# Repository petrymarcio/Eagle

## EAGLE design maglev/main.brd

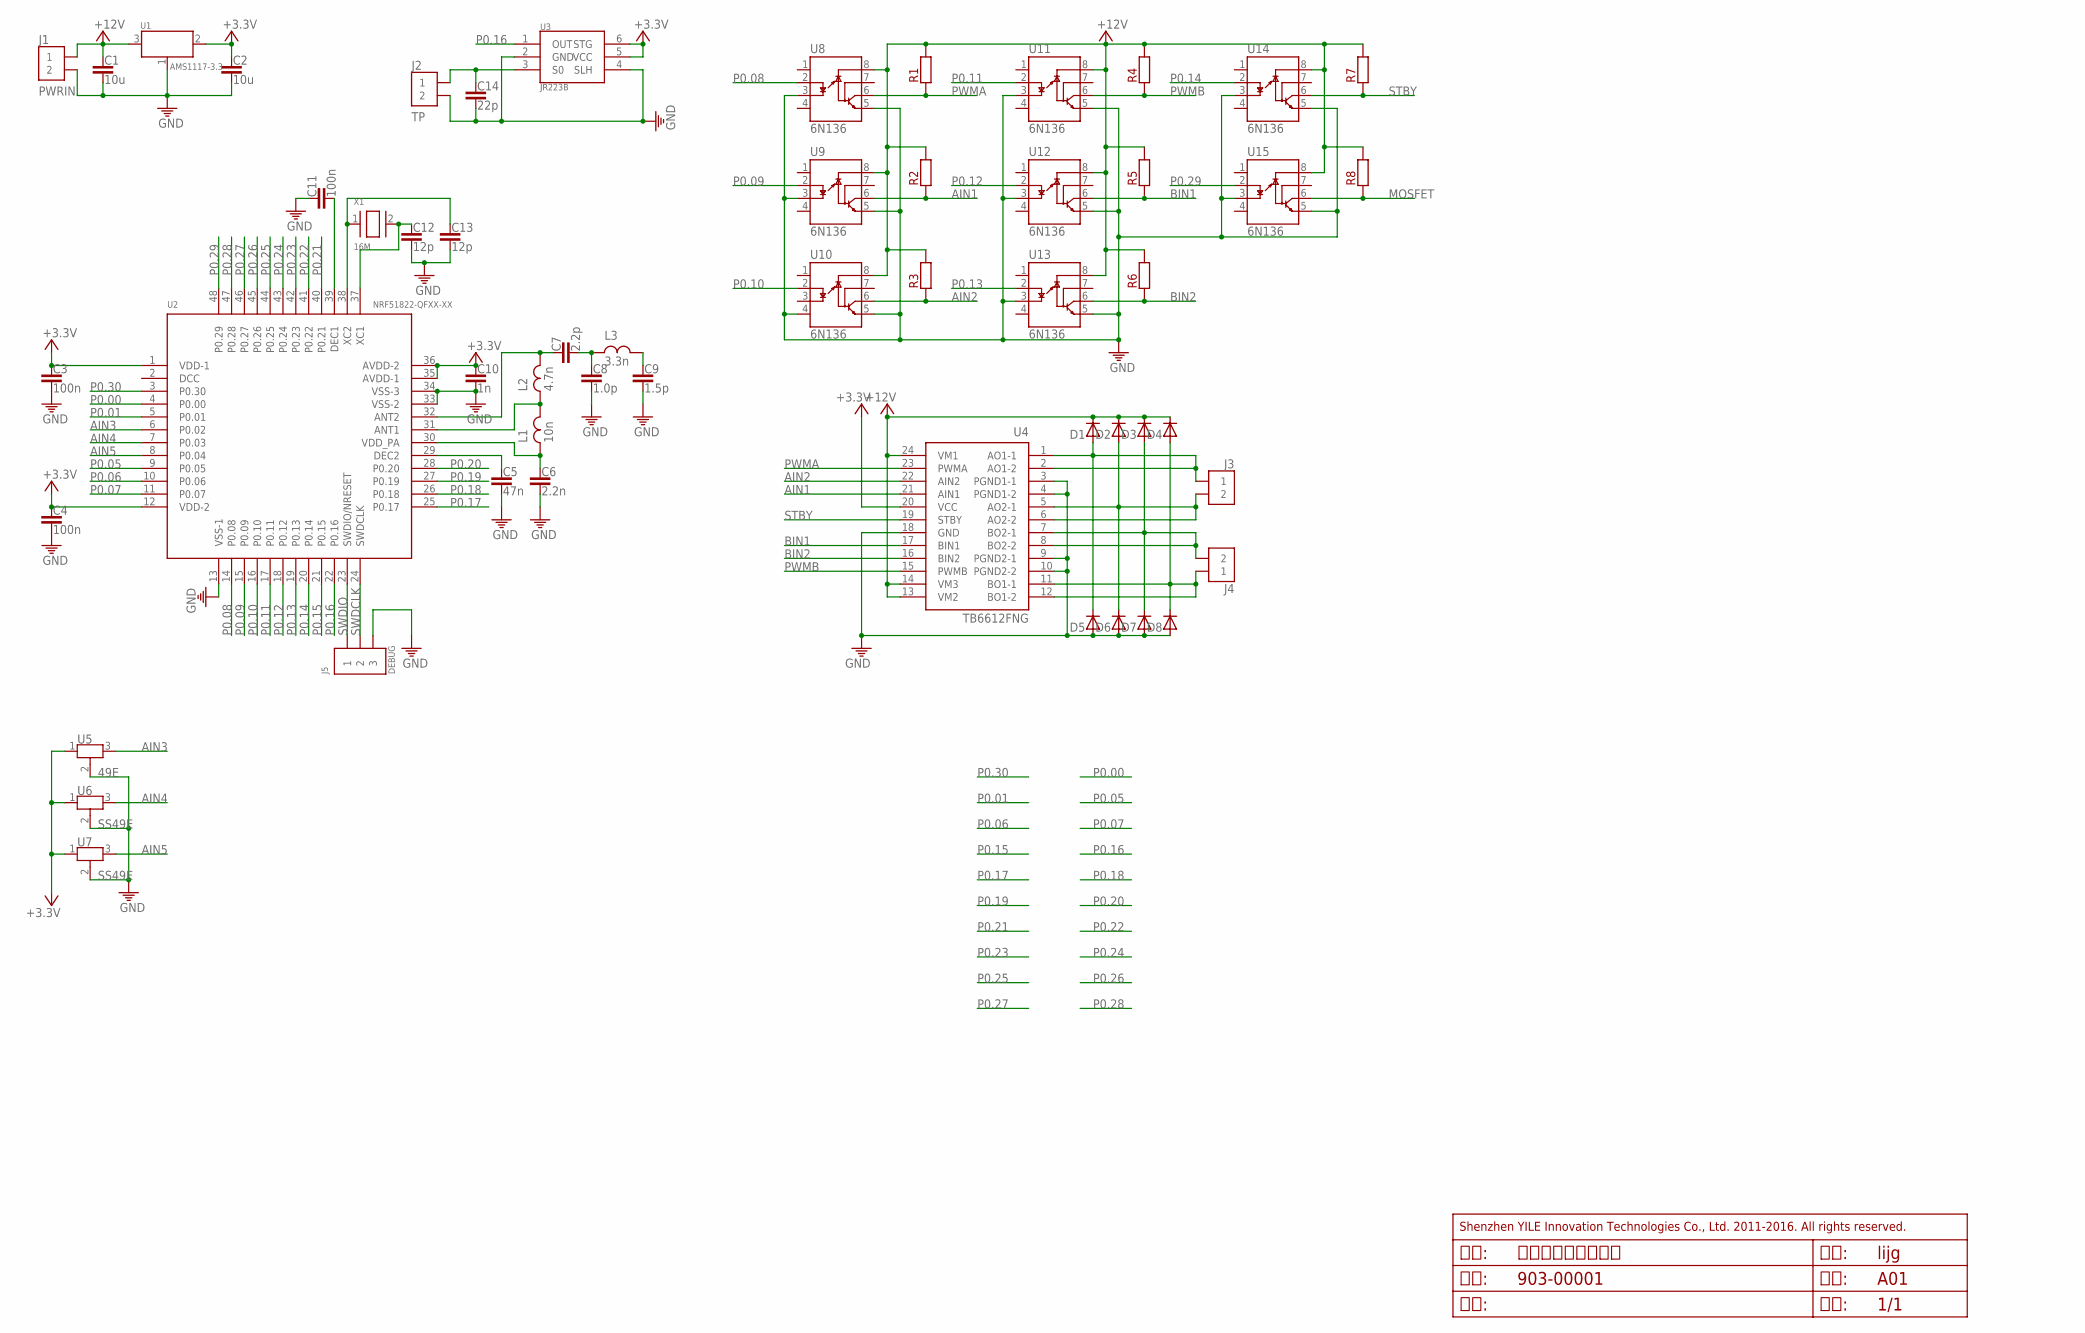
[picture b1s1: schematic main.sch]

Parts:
C1, C2: 10u; 0805
C3, C4, C11: 100n; 0805
C5: 47n; 0805
C6: 2.2n; 0805
C7: 2.2p; 0805
C8: 1.0p; 0805
C9: 1.5p; 0805
C10: 1n; 0805
C12, C13: 12p; 0805
C14: 22p; 0805
D1, D2, D3, D4, D5, D6, D7, D8: D0805; 0805
J1: PWRIN; SIP2-100
J2: TP; SIP2-100
J3, J4: CON2X12X1-DIP2-100; SIP2-100
J5: DEBUG; SIP3-100
L1: 10n; 0805
L2: 4.7n; 0805
L3: 3.3n; 0805
R1, R2, R3, R4, R5, R6, R7, R8: R0805; 0805
U1: AMS1117-3.3; SOT-223
U2: NRF51822-QFXX-XX; QFN48-6.0A-0.4A
U3: JR223B; SSOP6-P-118-0.6A
U4: TB6612FNG; SSOP24-P-300-0.65A
U5: 49E; AH3503
U6, U7: SS49E; AH3503
U8, U9, U10, U11, U12, U13, U14, U15: 6N136; SOP8-900A-2.54A
X1: 16M; S5032B

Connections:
+3.3V: C2.1, C3.1, C4.1, C10.1, U1.2 (VOUT), U2.1 (VDD-1), U2.12 (VDD-2), U2.35 (AVDD-1), U2.36 (AVDD-2), U3.5 (VCC), U3.6 (STG), U4.20 (VCC), U5.1, U6.1, U7.1
+12V: C1.1, D1.2, D2.2, D3.2, D4.2, J1.P$1 (1), R1.2, R2.2, R3.2, R4.2, R5.2, R6.2, R7.2, R8.2, U1.3 (VIN), U4.13 (VM2), U4.14 (VM3), U4.24 (VM1), U8.8 (VCC), U9.8 (VCC), U10.8 (VCC), U11.8 (VCC), U12.8 (VCC), U13.8 (VCC), U14.8 (VCC), U15.8 (VCC)
AIN1: R2.1, U4.21 (AIN1), U9.6 (VO)
AIN2: R3.1, U4.22 (AIN2), U10.6 (VO)
AIN3: U2.6 (P0.02), U5.3
AIN4: U2.7 (P0.03), U6.3
AIN5: U2.8 (P0.04), U7.3
BIN1: R5.1, U4.17 (BIN1), U12.6 (VO)
BIN2: R6.1, U4.16 (BIN2), U13.6 (VO)
GND: C1.2, C2.2, C3.2, C4.2, C5.2, C6.2, C8.2, C9.2, C10.2, C11.1, C12.2, C13.2, C14.2, D5.1, D6.1, D7.1, D8.1, J1.P$2 (2), J2.P$2 (2), J5.P$3 (3), U1.1 (GND/ADJ), U2.13 (VSS-1), U2.33 (VSS-2), U2.34 (VSS-3), U3.2 (GND), U3.4 (SLH), U4.3 (PGND1-1), U4.4 (PGND1-2), U4.9 (PGND2-1), U4.10 (PGND2-2), U4.18 (GND), U5.2, U6.2, U7.2, U8.3 (C), U8.5 (GND), U9.3 (C), U9.5 (GND), U10.4 (NC2), U10.5 (GND), U11.3 (C), U11.5 (GND), U12.3 (C), U12.5 (GND), U13.3 (C), U13.5 (GND), U14.3 (C), U14.5 (GND), U15.3 (C), U15.5 (GND)
MOSFET: R8.1, U15.6 (VO)
unnamed: C6.1, L1.1, U2.30 (VDD_PA)
unnamed: L1.2, L2.1, U2.31 (ANT1)
unnamed: C5.1, U2.29 (DEC2)
unnamed: C7.1, L2.2, U2.32 (ANT2)
unnamed: C7.2, C8.1, L3.1
unnamed: C14.1, J2.P$1 (1), U3.3 (S0)
unnamed: C12.1, U2.37 (XC1), X1.2 (X2)
unnamed: C13.1, U2.38 (XC2), X1.1 (X1)
unnamed: D1.1, D5.2, J3.P$1 (1), U4.1 (AO1-1), U4.2 (AO1-2)
unnamed: C11.2, U2.39 (DEC1)
unnamed: D2.1, D6.2, J3.P$2 (2), U4.5 (AO2-1), U4.6 (AO2-2)
unnamed: D3.1, D7.2, J4.P$2 (2), U4.7 (BO2-1), U4.8 (BO2-2)
unnamed: D4.1, D8.2, J4.P$1 (1), U4.11 (BO1-1), U4.12 (BO1-2)
P0.00: U2.4 (P0.00)
P0.01: U2.5 (P0.01)
P0.05: U2.9 (P0.05)
P0.06: U2.10 (P0.06)
P0.07: U2.11 (P0.07)
P0.08: U2.14 (P0.08), U8.2 (A)
P0.09: U2.15 (P0.09), U9.2 (A)
P0.10: U2.16 (P0.10), U10.2 (A)
P0.11: U2.17 (P0.11), U11.2 (A)
P0.12: U2.18 (P0.12), U12.2 (A)
P0.13: U2.19 (P0.13), U13.2 (A)
P0.14: U2.20 (P0.14), U14.2 (A)
P0.15: U2.21 (P0.15)
P0.16: U2.22 (P0.16), U3.1 (OUT)
P0.17: U2.25 (P0.17)
P0.18: U2.26 (P0.18)
P0.19: U2.27 (P0.19)
P0.20: U2.28 (P0.20)
P0.21: U2.40 (P0.21)
P0.22: U2.41 (P0.22)
P0.23: U2.42 (P0.23)
P0.24: U2.43 (P0.24)
P0.25: U2.44 (P0.25)
P0.26: U2.45 (P0.26)
P0.27: U2.46 (P0.27)
P0.28: U2.47 (P0.28)
P0.29: U2.48 (P0.29), U15.2 (A)
P0.30: U2.3 (P0.30)
PWMA: R1.1, U4.23 (PWMA), U8.6 (VO)
PWMB: R4.1, U4.15 (PWMB), U11.6 (VO)
STBY: R7.1, U4.19 (STBY), U14.6 (VO)
SWDCLK: J5.P$2 (2), U2.24 (SWDCLK)
SWDIO: J5.P$1 (1), U2.23 (SWDIO/NRESET)
WIRE: C9.1, L3.2

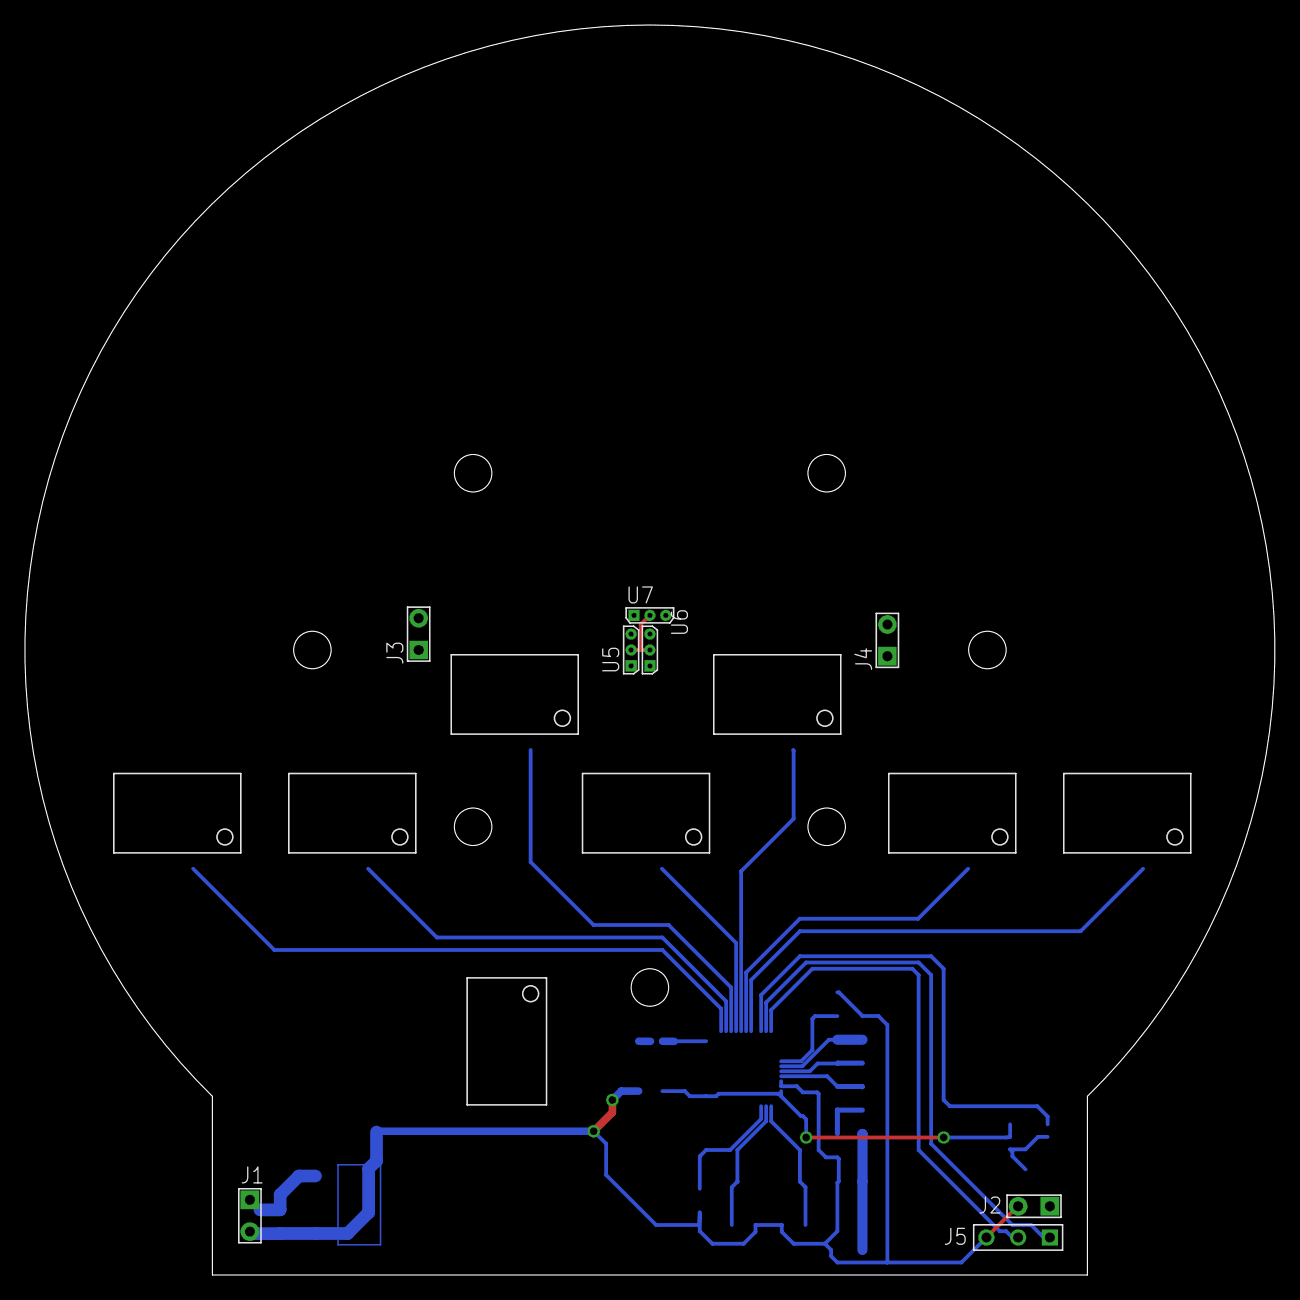
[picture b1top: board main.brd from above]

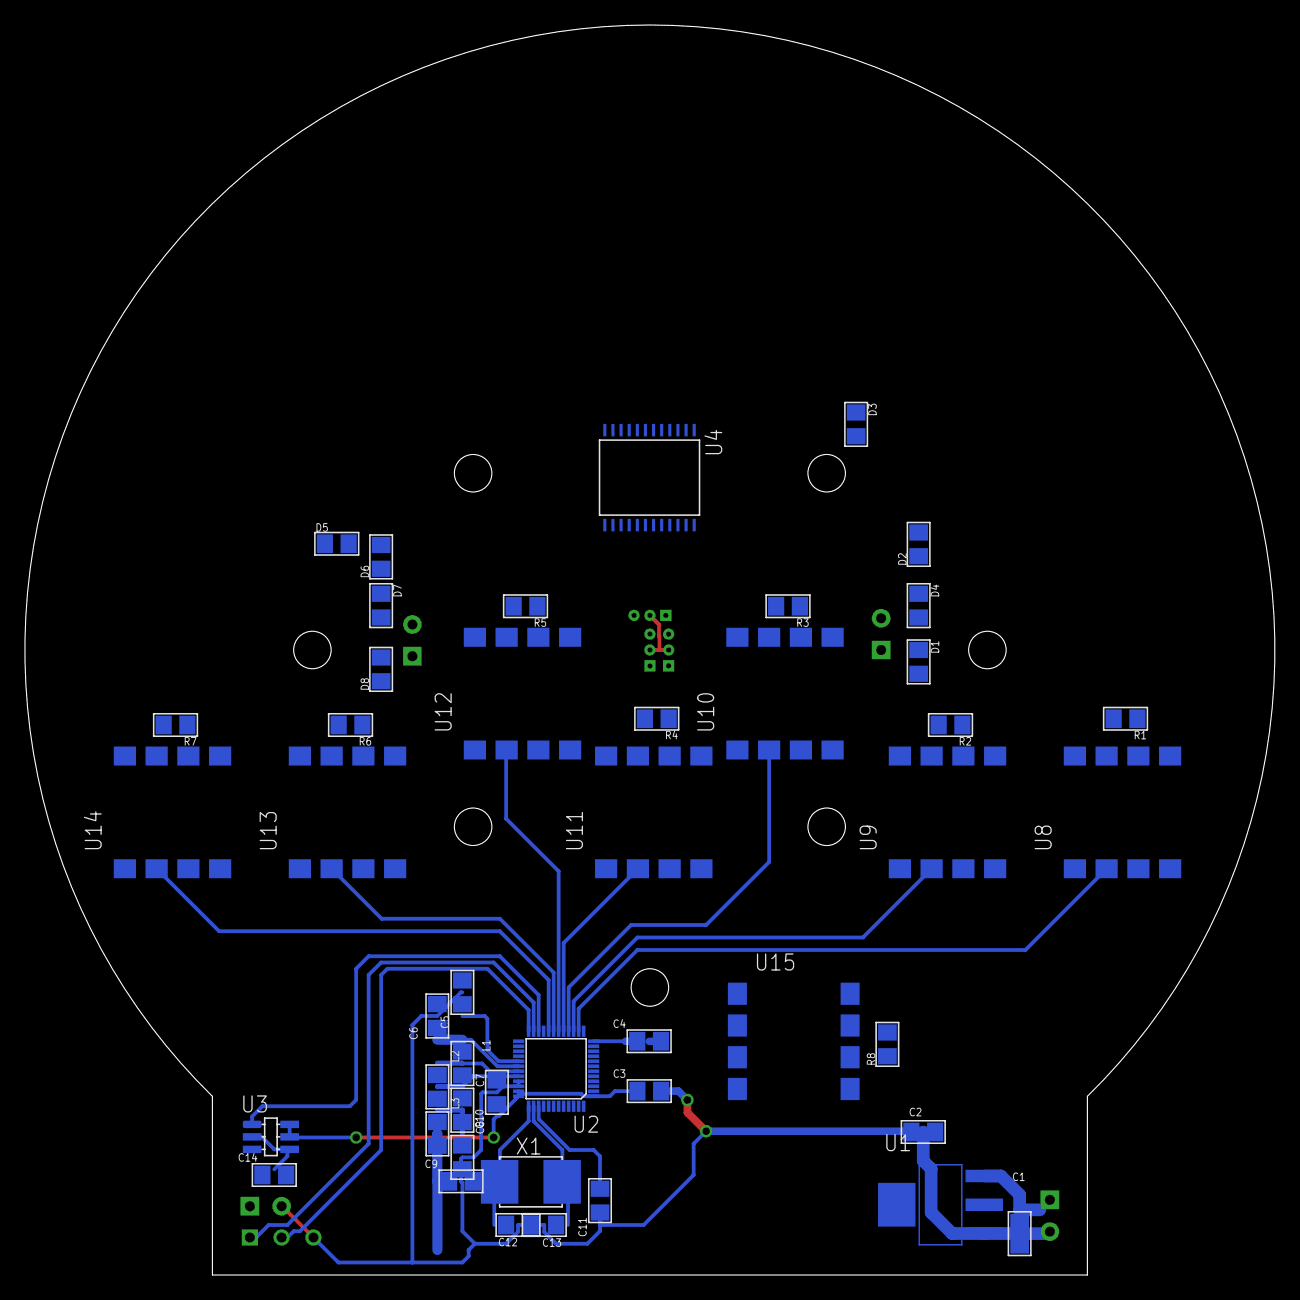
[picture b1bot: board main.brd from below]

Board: 2 copper layers, 100.0 x 100.0 mm, 54 parts (46 on the bottom side), 39 nets.

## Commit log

2016-03-31 add README.md

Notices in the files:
parts and their libraries:
frames: Shenzhen YILE Innovation Technologies Co., Ltd. 2011-2016. All rights reserved.
